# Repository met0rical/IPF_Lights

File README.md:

# IPF_Lights
Wireless remotes and base node for IPF lights

Designed to use an Arduino Nano as the base node with an NRF24L01+ radio.

Remote nodes are intended to be ATtiny84's with the NRF24L01+ radio following successful testing on the Nano.

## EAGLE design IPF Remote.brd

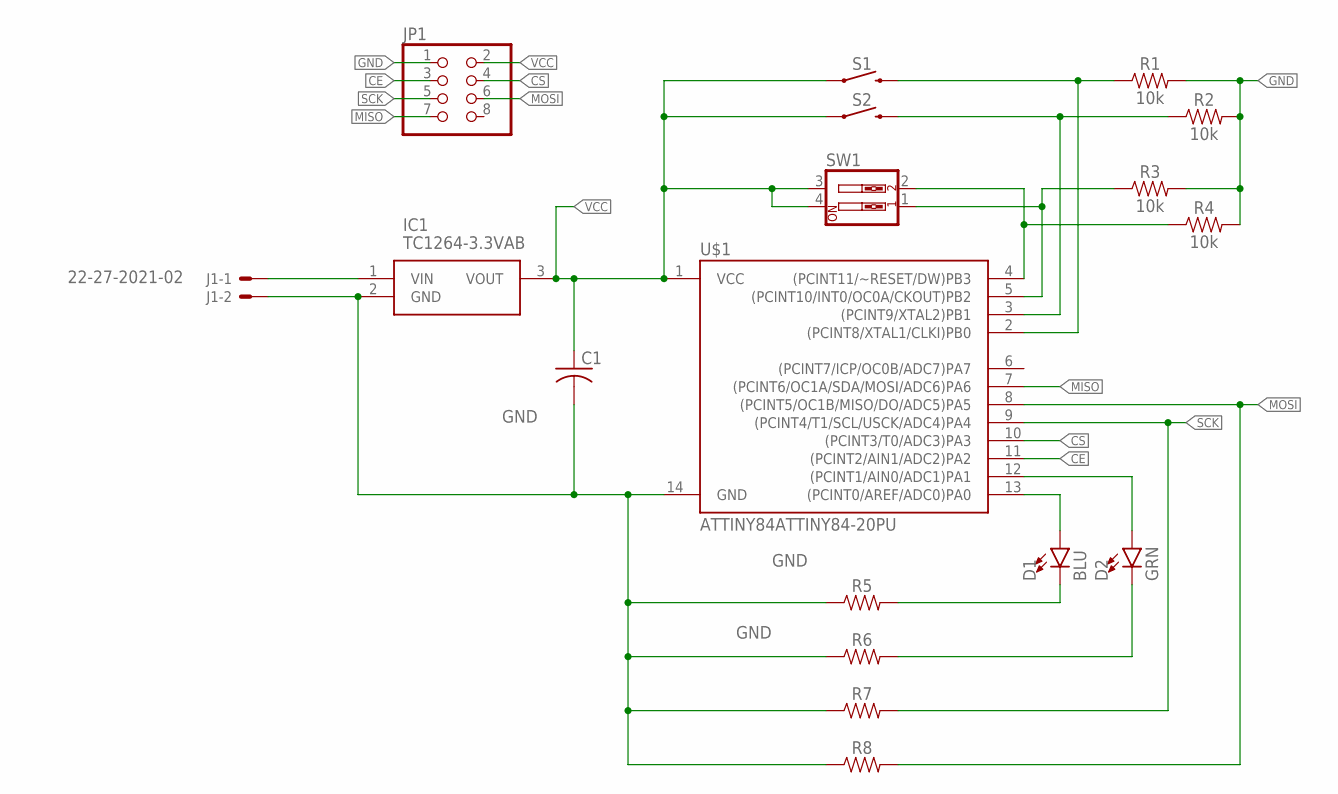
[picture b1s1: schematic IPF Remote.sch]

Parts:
C1: C-US025-024X044; C025-024X044
D1: BLU; LED_3MM
D2: GRN; LED_3MM
IC1: TC1264-3.3VAB; TO254P483X988X2222-3P
J1: 22-27-2021-02; 6410-02
JP1: PINHD-2X4; 2X04
R1, R2, R3, R4: 10k; AXIAL-0.3
R5, R6, R7, R8: AXIAL-0.3
S1, S2: MOMENTARY-SWITCH-SPST-PTH-6.0MM; TACTILE_SWITCH_PTH_6.0MM
SW1: SW_DIP-2; EDG-02
U$1: ATTINY84ATTINY84-20PU; DIP14

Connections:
CE: JP1.3, U$1.11 ((PCINT2/AIN1/ADC2)PA2)
CS: JP1.4, U$1.10 ((PCINT3/T0/ADC3)PA3)
GND: C1.2, IC1.2 (GND), J1.2, JP1.1, R1.P$2 (2), R2.P$2 (2), R3.P$2 (2), R4.P$2 (2), R5.P$1 (1), R6.P$1 (1), R7.P$1 (1), R8.P$1 (1), U$1.14 (GND)
MISO: JP1.7, U$1.7 ((PCINT6/OC1A/SDA/MOSI/ADC6)PA6)
MOSI: JP1.6, R8.P$2 (2), U$1.8 ((PCINT5/OC1B/MISO/DO/ADC5)PA5)
unnamed: IC1.1 (VIN), J1.1
unnamed: R2.P$1 (1), S2.3 (2), U$1.3 ((PCINT9/XTAL2)PB1)
unnamed: R3.P$1 (1), SW1.1, U$1.5 ((PCINT10/INT0/OC0A/CKOUT)PB2)
unnamed: R4.P$1 (1), SW1.2, U$1.4 ((PCINT11/~RESET/DW)PB3)
unnamed: R1.P$1 (1), S1.3 (2), U$1.2 ((PCINT8/XTAL1/CLKI)PB0)
unnamed: D1.A, U$1.13 ((PCINT0/AREF/ADC0)PA0)
unnamed: D2.A, U$1.12 ((PCINT1/AIN0/ADC1)PA1)
unnamed: D1.K (C), R5.P$2 (2)
unnamed: D2.K (C), R6.P$2 (2)
SCK: JP1.5, R7.P$2 (2), U$1.9 ((PCINT4/T1/SCL/USCK/ADC4)PA4)
VCC: C1.1, IC1.3 (VOUT), JP1.2, S1.1, S2.1, SW1.3, SW1.4, U$1.1 (VCC)

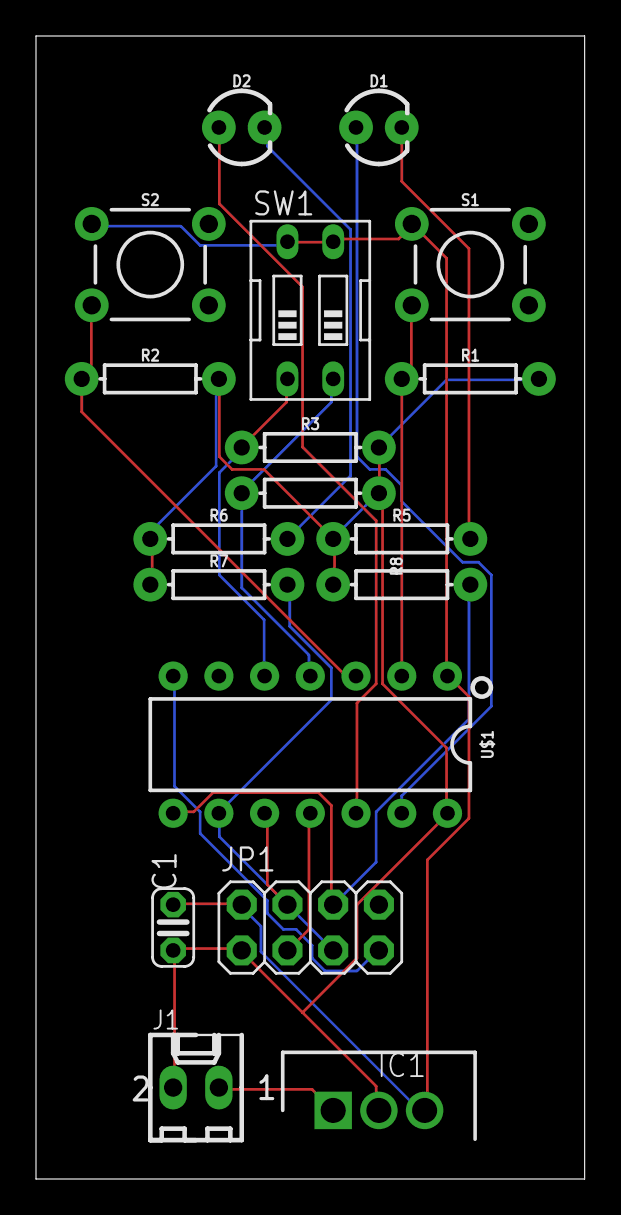
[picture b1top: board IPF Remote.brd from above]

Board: 2 copper layers, 30.5 x 63.5 mm, 18 parts (0 on the bottom side), 16 nets.

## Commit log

2019-04-23 Updated following RL testing
2019-04-24 Added timeout mode

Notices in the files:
parts and their libraries:
SparkFun-LED: Licensing: Creative Commons ShareAlike 4.0 International - https://creativecommons.org/licenses/by-sa/4.0
